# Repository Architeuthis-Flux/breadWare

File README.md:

# breadWare

# The vastly improved version of this is now [Jumperless](https://github.com/Architeuthis-Flux/Jumperless)
### This the early prototype version, and this lays out my thinking more on some fundamental desisions.

#### I've changed this project's name for version 3
The code and KiCAD files for the most recent revision are in the Jumperless folder. When I do a thorough writeup I may make an entirely new repo just so everythings stays clean. But for now, here's the new board and GUI 

# breadWare v0.2 
#### [Here's a link to the Hackaday.io project page](https://hackaday.io/project/180394-breadware)

My reason for doing this whole writeup and putting this out there is to hopefully find some fellow hackers who are equally stoked on breadWare and want to help make it into something where people will wonder how the hell they built anything before it existed (probably not Arduino levels of disruption, but when I need to use a Bus Pirate, I can't even imagine the horrible dystopian hellscape the world would be without it.) At least for me, placing jumpers messes up my flow, because there's always that angel on one shoulder telling me to be methodical: cut my jumpers to the right length, make nice 90° bends, use colors consistently, while the demon on the other shoulder says to just get the damn thing working now and let future me deal with the mess. The demon always wins, so I'd really like the angel to shut up, it's distracting. So offloading that internal debate to a computer seems like a good idea [disclaimer: do not run this on a HAL 9000 computer, I hear cognitive dissonance like this can cause undefined behavior]

So here's the second board revision. I was showing the [last version](breadWare/v0.1-alpha/) off to someone and they offhandedly mentioned that it would be cool if the whole thing fit under the breadboard. I knew this was my plan all along, but it forced me to finally design it before the code gets too specific to the original off-the-cuff design and I get stuck with my poor ~~life~~ design choices. 

## Matrix Board

I found that the most valuable resource when finding paths between rows that aren't directly connected (so they need to make an intermediate hop) are "virtual" breadboard rows that aren't connected to the actual board but connect to the control board below and basically act as the general purpose nodes to do everything else (like reading voltages, connecting to the GPIO on the microcontroller, connecting to a second board, etc.). I put 4 of them in (on chips A, D, E, H), and I don't think that's nearly enough if I want to be able to do a bunch of special function things at once without making the user use some particular set of rows to do certain things. I would really like to make it as simple as "put anything wherever and the board will figure it out."

I changed the logical arrangement of the [MT8816](https://www.futurlec.com/Datasheet/Zarlink/MT8816AE.pdf) crosspoint switches to make the it easier to just hop over the middle space. In the original layout if I wanted to connect top row 5 to bottom row 5, it would always take 2 hops to do that (and these switches each have an on resistance of about 65Ω). Now the bottom rows are flipped so internally the bottom left is 62 and counts down to 33 on the right (note: these are abstracted away to the user by using b1-b30 instead of bigger numbers.)

And just to add some glam I added some reverse mounted LEDs that shine through the top and bottom power rails to show when that rail's power supply is on.

## Control Board

I almost entirely redesigned the controller board so it has a ton of whatever the hardware equivalent of syntactic sugar is. The original was kind of thrown together to make sure the concept of using crosspoint switches like that wasn't fundamentally stupid (still not entirely ruling that out, but so far it looks promising.) I also just realized I never did a writeup for the first iteration, and I'm not about to go back and do that just to prove that this board is an improvement.

### Power Stuff
Because I'm going to such great lengths to make everything analog, and I already need a negative supply for the crosspoint switches; I decided to make the adjustable power supply for the rails also be able to do negative voltages. The power stuff still needs some work, right now it gets pretty warm when it's running and it really doesn't like it when I remove the matrix board with it on. Presumably because it needs some current draw but I'm not exactly sure why it cares as much as it does (I burned a tantalum cap shaped brand into my finger, you could almost read the markings in it.) 

Also, the range of voltages available to each of the 4 rails is fixed. Next revision might include some way to multiplex the power rails (allowing any of them to be negative, right now only the bottom negative rail can do that and it can be changed with a solder jumper) but having looked into it for a while, there doesn't seem to be a way to do it simply enough to outweigh the small utility gained from it. If anyone knows a better way to do this, let me know.

I'm using an [LT1054](https://www.ti.com/lit/ds/symlink/lt1054.pdf) switched capacitor bipolar voltage converter that takes in +5V and doubles it to +10V and also flips that to -10V. That powers the MT8816s directly and the op amps I'm using for the adjustable voltage supplies. The previous board used inductors for that, and aside from the electrical noise, you could hear them running. I know the frequency they run at is way higher than 20kHz but they must have been resonating with something (or I'm actually part bat) because it was super annoying.

The way I decided to make an adjustable supply that can be controlled by the mcu might be really dumb, but so far it seems to work. I didn't find any well documented examples of people doing it this way, so I'd love to hear from anyone who has or has a good reason why it will cause problems. 

I used an [MCP4728](http://ww1.microchip.com/downloads/en/devicedoc/22187e.pdf) DAC that's controlled by I2C and feeds it's 4 outputs into 2 [L272D](https://www.st.com/resource/en/datasheet/l272.pdf) power op amps that can apparently supply 1A each. I used the inverting arrangement with a gain of 1.6 to make the negative supply able to supply 0V - -8V from the 0V - +5V output from the DAC. I put a bunch of low voltage drop schottkys (or is it schottkies? weird) so whatever is happening on the power rails they're supplying shouldn't affect them too much. 

What's cool about this setup is that the DAC is fast enough to use this whole circuit as a DDS function generator. That's why I put solder jumpers to disconnect all the bypass caps. I haven't written the code to try this out yet though. 

### Special Functions

On the control board there's another 8x16 crosspoint switch that I'm using to multiplex the 8 passthrough connections (1 per chip on the top matrix board, but only 4 of them aren't connected to a breadboard pin) to the special functions on the bottom control board. 

The special functions are (a checkmark means the firmware is written enough to use it):
 [ ] 2 ADC channels that can be read by the microcontroller 
 [x] 2 digital potentiometer channels using an [MCP4661](https://ww1.microchip.com/downloads/en/DeviceDoc/22107B.pdf) 
 [ ] 5 GPIO pins directly connected to the [ATmega4809](http://ww1.microchip.com/downloads/en/DeviceDoc/ATmega4808-4809-Data-Sheet-DS40002173A.pdf)
 [x] 2 adjustable power supply channels (0 - 5V, 0 - -8V)
 [x] 1 ground

The 2 ADC channels go through two 4:1 voltage dividers to bring a possible ±10V input down to ±2.5V and the bottom of those dividers are connected to the V_REF pin on the microcontroller so analog signals can be biased to 0-5V to be read by the 10-bit ADC. 

There's an [MCP4661](https://ww1.microchip.com/downloads/en/DeviceDoc/22107B.pdf) dual 8 bit digital potentiometer that has all 3 pins on 2 independent pots connected to the special function switch. I need to come up with a better interface for setting it in the terminal menu. When I eventually get around to making a GUI for this it will definitely make these more useful. These also come in 4 different ranges (5K, 10K, 50K, 100K) with the same pinout, I currently have the 50K model in there so that means each step is 195 ohms.

The GPIO pins are super interesting, for some reason the [ATmega4809](http://ww1.microchip.com/downloads/en/DeviceDoc/ATmega4808-4809-Data-Sheet-DS40002173A.pdf) datasheet never mentions the clear superiority of the first 4 pins in port C. 

PC0-3 can do I2C, U(S)ART, 16-bit Timer/Counter, PWM, SPI, and CCL-LUT! 
The CCL-LUT means Configurable Custom Logic - LookUp Table, so that means it an simulate an arbitrary logic gate. The analog stuff is covered by pin PE3. 

Now the tricky part is coming up with a nice way to use those functions through the serial connection. I could probably somehow port the Bus Pirate firmware into some sort of shell, so you could use their awesome Community Firmware (and the red PCB really sells the aesthetic.) 

Also, if anyone from Dangerous Prototypes is reading this; I'm dying for updates on (or just an official crushing of my dreams of one day owning) the [Bus Pirate Ultra](http://dangerousprototypes.com/forum/index.php?topic=10316.0)

### Communicating With Other Things

On each corner of the board I put a 2x2 header so you can connect these side-by-side and make these into longer board. They communicate via UART with Tx Rx in at the top left and Tx Rx out at the top right. The bottom corners have the 4 unconnected pins from the top matrix on both sides. So you could use these to make connections from one board to the other. As it is currently, having only 4 of these general purpose matrix connections is a huge bottleneck for doing just about anything so I probably need to come up with a way to have more of these free pins in the next revision. 

To communicate with the computer, I'm using an [MCP2221A](http://ww1.microchip.com/downloads/en/devicedoc/20005565b.pdf) to talk to the mcu via a dedicated UART. That chip is also connected to the I2C lines but I'm not sure what I'm going to use that for, maybe I'll have the I2C traffic passed along in some sort of debug mode. It also can send a reset signal from one of it's 4 GPIO lines to the ATmega4809 (with a solder jumper in case that causes problems), which notably is a missing feature of this chip. 
I could pretend that my choice to to use this was some principled stand against FTDI to cover for the fact that I actually don't remember why I chose this over and FTDI232.

## Making It Do Stuff

The interface currently sort of follows the general format that a Bus Pirate (and I'm sure a bunch of other things) use; mostly single character commands that present a sub menu. It's amazing how quickly you run out of letters that make sense for a particular command, especially when you have some command you want to be available globally. 

Making connections on the board just requires you to type in the two rows you want to connect, separated by a comma. Rows on the bottom are preceded by a 'b' so if you want to connect the 12th row on the top to the 24th row on the bottom you just type
 > 12,b24

In the near future I intend to make a full blown GUI for this, because that's the part that will make this thing actually make your life easier.

Here are some screenshots the interface:

Connecting Nodes

Disconnecting Nodes

Turning on the power supplies

Using the potentiometer

Showing the frontend connections you've made

Showing the backend (chip to chip) connections 

Here are some extra glamour shots:

mmmmmm melty traces

 > btw most of these photos were taken on Lomochrome Metropolis with a Mamiya RB67
 > the two showing the boards separately were taken with an Intrepid 4x5 on cross-processed Provia 100f
 > you can download ridiculously huge scans of these (or my non-documentation related photos) from my [Flickr](https://www.flickr.com/photos/arabidsquid/)

## [Here's the documentation for v0.1](breadWare/v0.1-alpha/)

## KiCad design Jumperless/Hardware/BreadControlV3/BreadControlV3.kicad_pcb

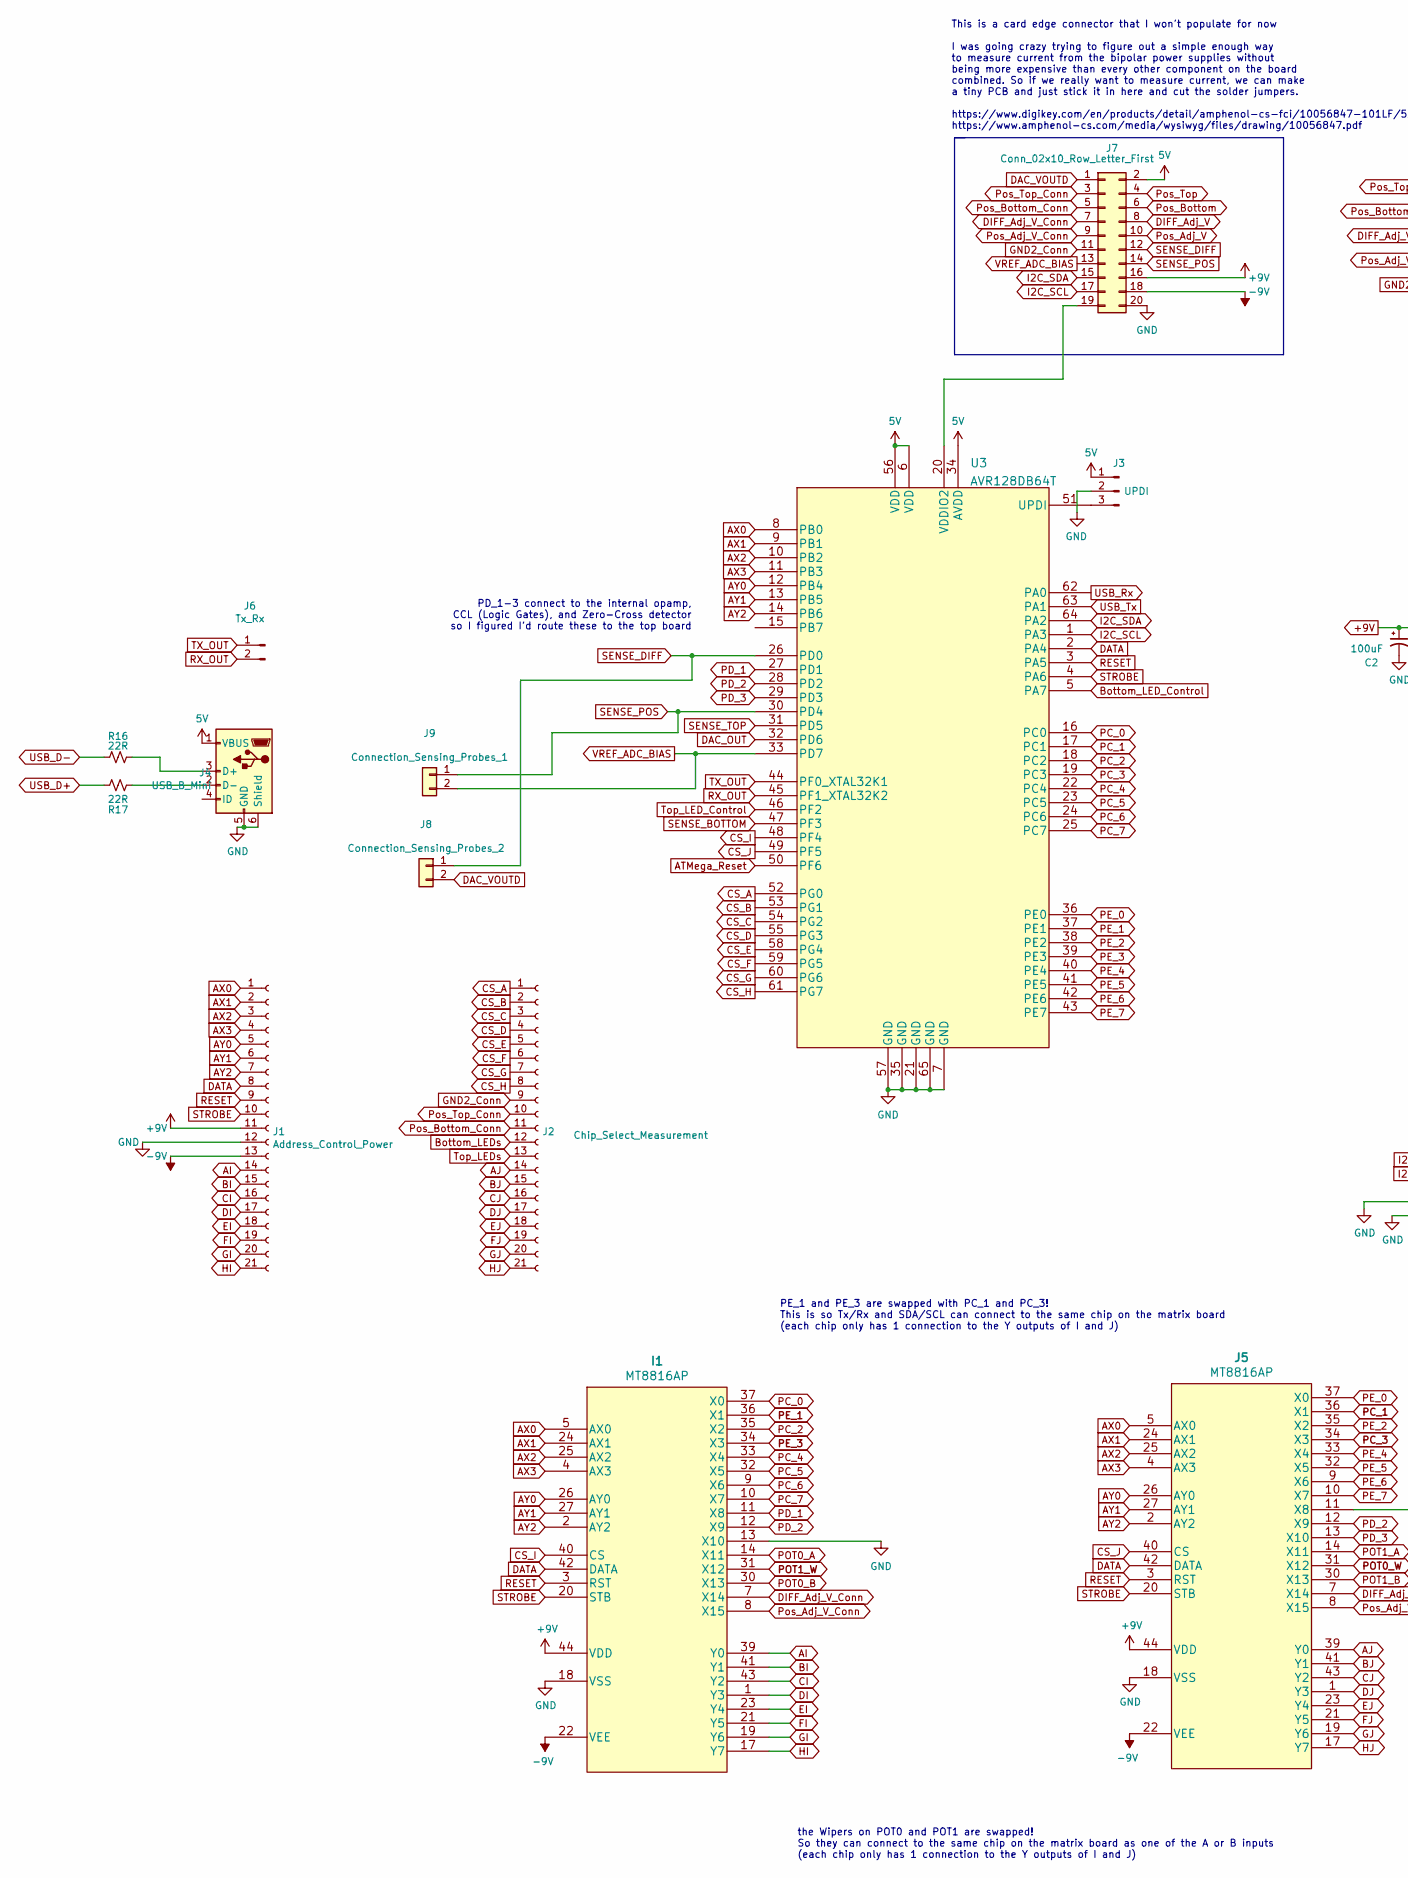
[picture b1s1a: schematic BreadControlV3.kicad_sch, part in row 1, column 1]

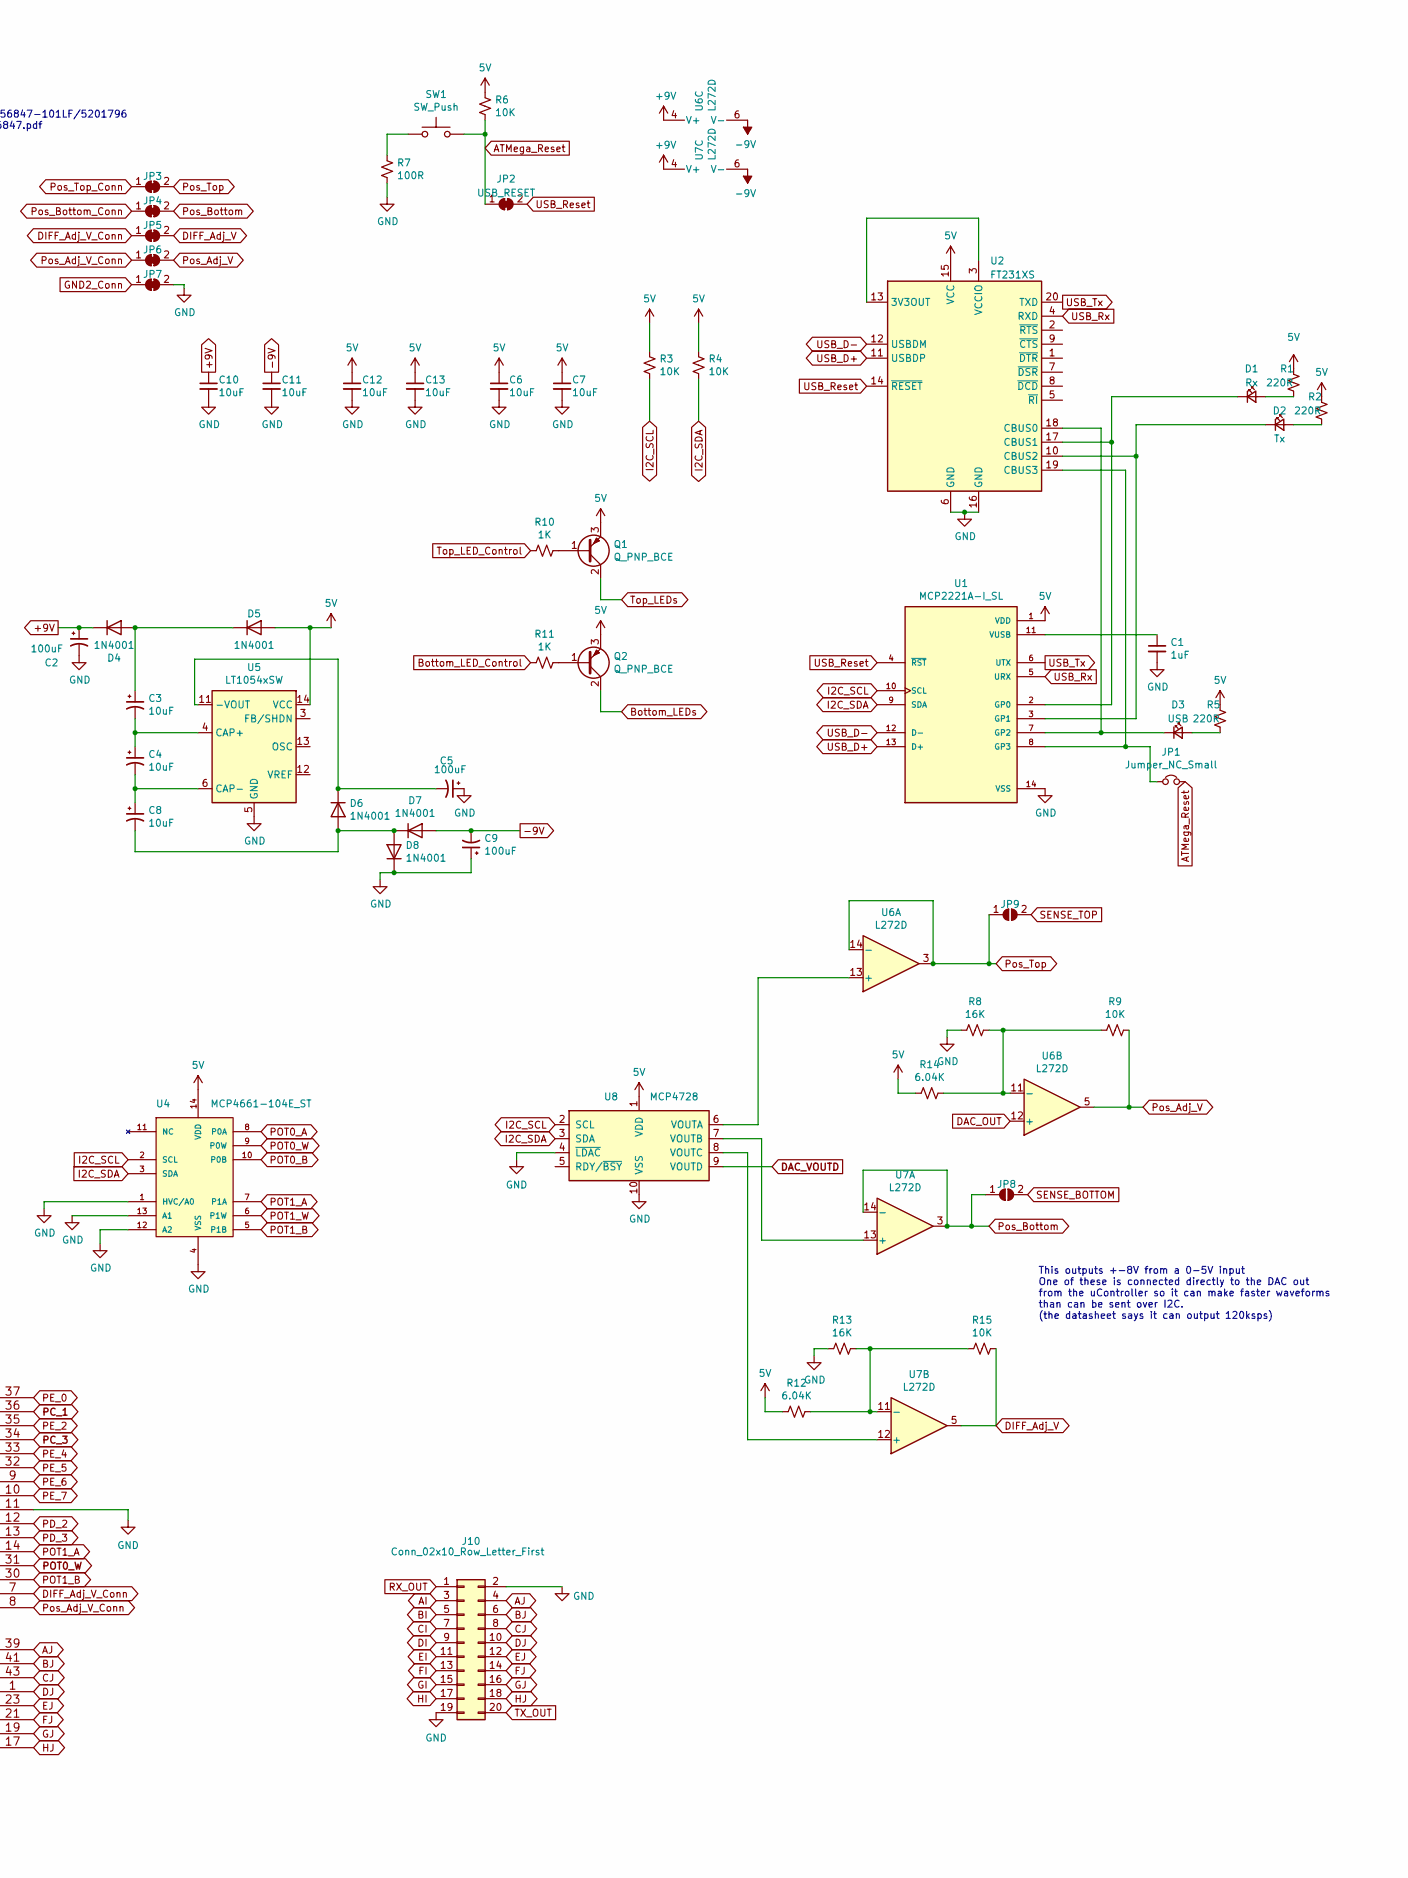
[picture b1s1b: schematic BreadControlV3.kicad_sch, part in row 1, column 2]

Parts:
C1: 1uF; C_0805_2012Metric_Pad1.18x1.45mm_HandSolder
C2, C5, C9: 100uF; C_1206_3216Metric_Pad1.33x1.80mm_HandSolder
C3, C4, C8: 10uF; CP_EIA-6032-20_AVX-F_Pad2.25x2.35mm_HandSolder
C6, C7, C10, C11, C12, C13: 10uF; C_0805_2012Metric_Pad1.18x1.45mm_HandSolder
D1: Rx; D_0805_2012Metric_Pad1.15x1.40mm_HandSolder
D2: Tx; D_0805_2012Metric_Pad1.15x1.40mm_HandSolder
D3: USB; D_0805_2012Metric_Pad1.15x1.40mm_HandSolder
D4, D5, D6, D7, D8: 1N4001; D_SOD-123
I1: MT8816AP; PLCC-44_16.6x16.6mm_P1.27mm
J1: Address_Control_Power; PinHeader_1x21_P2.54mm_Vertical
J2: Chip_Select_Measurement; PinHeader_1x21_P2.54mm_Vertical
J3: UPDI; PinHeader_1x03_P2.54mm_Vertical
J4: USB_B_Mini; USB_Mini-B_Wuerth_65100516121_Horizontal
J5: MT8816AP; PLCC-44_16.6x16.6mm_P1.27mm
J6: Tx_Rx; PinHeader_1x02_P2.54mm_Vertical
J7, J10: Conn_02x10_Row_Letter_First; 10056847-101LF
J8: Connection_Sensing_Probes_2; PinHeader_1x02_P2.54mm_Vertical
J9: Connection_Sensing_Probes_1; PinHeader_1x02_P2.54mm_Vertical
JP1: Jumper_NC_Small; SolderJumper-2_P1.3mm_Bridged_RoundedPad1.0x1.5mm
JP2: USB_RESET; SolderJumper-2_P1.3mm_Bridged_RoundedPad1.0x1.5mm
JP3, JP4, JP5, JP6, JP7: SolderJumper_2_Bridged; SolderJumper-2_P1.3mm_Bridged_RoundedPad1.0x1.5mm
JP8, JP9: SolderJumper_2_Open; SolderJumper-2_P1.3mm_Open_RoundedPad1.0x1.5mm
Q1, Q2: Q_PNP_BCE; SOT-23
R1, R2, R5: 220R; R_0805_2012Metric_Pad1.20x1.40mm_HandSolder
R3, R4, R6, R9, R15: 10K; R_0805_2012Metric_Pad1.20x1.40mm_HandSolder
R7: 100R; R_0805_2012Metric_Pad1.20x1.40mm_HandSolder
R8, R13: 16K; R_0805_2012Metric_Pad1.20x1.40mm_HandSolder
R10, R11: 1K; R_0805_2012Metric_Pad1.20x1.40mm_HandSolder
R12, R14: 6.04K; R_0805_2012Metric_Pad1.20x1.40mm_HandSolder
R16, R17: 22R; R_0805_Optional_Bridged
SW1: SW_Push; SW_SPST_PTS645
U1: MCP2221A-I_SL; SOIC-14_3.9x8.7mm_P1.27mm
U2: FT231XS; SSOP-20_3.9x8.7mm_P0.635mm
U3: AVR128DB64T; VQFN-64-1EP_9x9mm_P0.5mm_EP7.15x7.15mm
U4: MCP4661-104E_ST; TSSOP-14_4.4x5mm_P0.65mm; MPN MCP4661-104E/ST
U5: LT1054xSW; SOIC-16W_7.5x10.3mm_P1.27mm
U6, U7: L272D; SOIC-16_3.9x9.9mm_P1.27mm
U8: MCP4728; MSOP-10_3x3mm_P0.5mm

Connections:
5V: C6.1, C7.1, C12.1, C13.1, D5.2 (A), J3.1, J4.1 (VBUS), J7.2, Q1.3 (E), Q2.3 (E), R1.1, R2.1, R3.1, R4.1, R5.1, R6.1, R12.1, R14.1, U1.1 (VDD), U2.15 (VCC), U3.6 (VDD), U3.34 (AVDD), U3.56 (VDD), U4.14 (VDD), U5.14 (VCC), U8.1 (VDD)
+9V: C2.1, C10.1, D4.1 (K), I1.44 (VDD), J1.11, J5.44 (VDD), J7.16, U6.4 (V+), U7.4 (V+)
-9V: C9.2, C11.1, D7.2 (A), I1.22 (VEE), J1.13, J5.22 (VEE), J7.18, U6.6 (V-), U7.6 (V-)
AI: I1.39 (Y0), J1.14, J10.3
AJ: J2.14, J5.39 (Y0), J10.4
ATMega_Reset: JP1.2, JP2.1 (A), R6.2, SW1.2, U3.50 (PF6)
AX0: I1.5 (AX0), J1.1, J5.5 (AX0), U3.8 (PB0)
AX1: I1.24 (AX1), J1.2, J5.24 (AX1), U3.9 (PB1)
AX2: I1.25 (AX2), J1.3, J5.25 (AX2), U3.10 (PB2)
AX3: I1.4 (AX3), J1.4, J5.4 (AX3), U3.11 (PB3)
AY0: I1.26 (AY0), J1.5, J5.26 (AY0), U3.12 (PB4)
AY1: I1.27 (AY1), J1.6, J5.27 (AY1), U3.13 (PB5)
AY2: I1.2 (AY2), J1.7, J5.2 (AY2), U3.14 (PB6)
BI: I1.41 (Y1), J1.15, J10.5
BJ: J2.15, J5.41 (Y1), J10.6
Bottom_LED_Control: R11.2, U3.5 (PA7)
Bottom_LEDs: J2.12, Q2.2 (C)
CI: I1.43 (Y2), J1.16, J10.7
CJ: J2.16, J5.43 (Y2), J10.8
CS_A: J2.1, U3.52 (PG0)
CS_B: J2.2, U3.53 (PG1)
CS_C: J2.3, U3.54 (PG2)
CS_D: J2.4, U3.55 (PG3)
CS_E: J2.5, U3.58 (PG4)
CS_F: J2.6, U3.59 (PG5)
CS_G: J2.7, U3.60 (PG6)
CS_H: J2.8, U3.61 (PG7)
CS_I: I1.40 (CS), U3.48 (PF4)
CS_J: J5.40 (CS), U3.49 (PF5)
DAC_OUT: U3.32 (PD6), U6.12 (+)
DAC_VOUTD: J7.1, J8.2, U8.9 (VOUTD)
DATA: I1.42 (DATA), J1.8, J5.42 (DATA), U3.2 (PA4)
DI: I1.1 (Y3), J1.17, J10.9
DIFF_Adj_V: J7.8, JP5.2 (B), R15.2, U7.5
DIFF_Adj_V_Conn: I1.7 (X14), J5.7 (X14), J7.7, JP5.1 (A)
DJ: J2.17, J5.1 (Y3), J10.10
EI: I1.23 (Y4), J1.18, J10.11
EJ: J2.18, J5.23 (Y4), J10.12
FI: I1.21 (Y5), J1.19, J10.13
FJ: J2.19, J5.21 (Y5), J10.14
GI: I1.19 (Y6), J1.20, J10.15
GJ: J2.20, J5.19 (Y6), J10.16
GND: C1.2, C2.2, C5.1, C6.2, C7.2, C9.1, C10.2, C11.2, C12.2, C13.2, D8.1 (K), I1.13 (X10), I1.18 (VSS), J1.12, J3.2, J4.5 (GND), J4.6 (Shield), J5.11 (X8), J5.18 (VSS), J7.20, J10.2, J10.19, JP7.2 (B), R7.2, R8.1, R13.1, U1.14 (VSS), U2.6 (GND), U2.16 (GND), U3.7 (GND), U3.21 (GND), U3.35 (GND), U3.57 (GND), U3.65 (GND), U4.1 (HVC/A0), U4.4 (VSS), U4.12 (A2), U4.13 (A1), U5.5 (GND), U8.4 (~LDAC), U8.10 (VSS)
GND2_Conn: J2.9, J7.11, JP7.1 (A)
HI: I1.17 (Y7), J1.21, J10.17
HJ: J2.21, J5.17 (Y7), J10.18
I2C_SCL: J7.17, R3.2, U1.10 (SCL), U3.1 (PA3), U4.2 (SCL), U8.2 (SCL)
I2C_SDA: J7.15, R4.2, U1.9 (SDA), U3.64 (PA2), U4.3 (SDA), U8.3 (SDA)
unnamed: C1.1, U1.11 (VUSB)
unnamed: C3.1, D4.2 (A), D5.1 (K)
unnamed: C3.2, C4.1, U5.4 (CAP+)
unnamed: C4.2, C8.1, U5.6 (CAP-)
unnamed: C5.2, D6.1 (K), U5.11 (-VOUT)
unnamed: C8.2, D6.2 (A), D7.1 (K), D8.2 (A)
unnamed: D1.1 (K), U1.2 (GP0), U2.17 (CBUS1)
unnamed: D1.2 (A), R1.2
unnamed: D2.1 (K), U1.3 (GP1), U2.10 (CBUS2)
unnamed: D2.2 (A), R2.2
unnamed: D3.1 (K), U1.7 (GP2), U2.18 (CBUS0)
unnamed: D3.2 (A), R5.2
unnamed: J3.3, U3.51 (UPDI)
unnamed: J4.2 (D-), R17.1
unnamed: J4.3 (D+), R16.1
unnamed: J7.19, U3.20 (VDDIO2)
unnamed: JP1.1, U1.8 (GP3), U2.19 (CBUS3)
unnamed: Q1.1 (B), R10.1
unnamed: Q2.1 (B), R11.1
unnamed: R7.1, SW1.1
unnamed: R12.2, R13.2, R15.1, U7.11 (-)
unnamed: R8.2, R9.1, R14.2, U6.11 (-)
unnamed: U2.3 (VCCIO), U2.13 (3V3OUT)
unnamed: U6.13 (+), U8.6 (VOUTA)
unnamed: U7.12 (+), U8.8 (VOUTC)
unnamed: U7.13 (+), U8.7 (VOUTB)
PC_0: I1.37 (X0), U3.16 (PC0)
PC_1: J5.36 (X1), U3.17 (PC1)
PC_2: I1.35 (X2), U3.18 (PC2)
PC_3: J5.34 (X3), U3.19 (PC3)
PC_4: I1.33 (X4), U3.22 (PC4)
PC_5: I1.32 (X5), U3.23 (PC5)
PC_6: I1.9 (X6), U3.24 (PC6)
PC_7: I1.10 (X7), U3.25 (PC7)
PD_1: I1.11 (X8), U3.27 (PD1)
PD_2: I1.12 (X9), J5.12 (X9), U3.28 (PD2)
PD_3: J5.13 (X10), U3.29 (PD3)
PE_0: J5.37 (X0), U3.36 (PE0)
PE_1: I1.36 (X1), U3.37 (PE1)
PE_2: J5.35 (X2), U3.38 (PE2)
PE_3: I1.34 (X3), U3.39 (PE3)
PE_4: J5.33 (X4), U3.40 (PE4)
PE_5: J5.32 (X5), U3.41 (PE5)
PE_6: J5.9 (X6), U3.42 (PE6)
PE_7: J5.10 (X7), U3.43 (PE7)
POT0_A: I1.14 (X11), U4.8 (P0A)
POT0_B: I1.30 (X13), U4.10 (P0B)
POT0_W: J5.31 (X12), U4.9 (P0W)
POT1_A: J5.14 (X11), U4.7 (P1A)
POT1_B: J5.30 (X13), U4.5 (P1B)
POT1_W: I1.31 (X12), U4.6 (P1W)
Pos_Adj_V: J7.10, JP6.2 (B), R9.2, U6.5
Pos_Adj_V_Conn: I1.8 (X15), J5.8 (X15), J7.9, JP6.1 (A)
Pos_Bottom: J7.6, JP4.2 (B), JP8.1 (A), U7.3, U7.14 (-)
Pos_Bottom_Conn: J2.11, J7.5, JP4.1 (A)
Pos_Top: J7.4, JP3.2 (B), JP9.1 (A), U6.3, U6.14 (-)
Pos_Top_Conn: J2.10, J7.3, JP3.1 (A)
RESET: I1.3 (RST), J1.9, J5.3 (RST), U3.3 (PA5)
RX_OUT: J6.2, J10.1, U3.45 (PF1_XTAL32K2)
SENSE_BOTTOM: JP8.2 (B), U3.47 (PF3)
SENSE_DIFF: J7.12, J8.1, U3.26 (PD0)
SENSE_POS: J7.14, J9.1, U3.30 (PD4)
SENSE_TOP: JP9.2 (B), U3.31 (PD5)
STROBE: I1.20 (STB), J1.10, J5.20 (STB), U3.4 (PA6)
TX_OUT: J6.1, J10.20, U3.44 (PF0_XTAL32K1)
Top_LED_Control: R10.2, U3.46 (PF2)
Top_LEDs: J2.13, Q1.2 (C)
USB_D+: R17.2, U1.13 (D+), U2.11 (USBDP)
USB_D-: R16.2, U1.12 (D-), U2.12 (USBDM)
USB_Reset: JP2.2 (B), U1.4 (~RST), U2.14 (~RESET)
USB_Rx: U1.5 (URX), U2.4 (RXD), U3.62 (PA0)
USB_Tx: U1.6 (UTX), U2.20 (TXD), U3.63 (PA1)
VREF_ADC_BIAS: J7.13, J9.2, U3.33 (PD7)

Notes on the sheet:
This is a card edge connector that I won't populate for now I was going crazy trying to figure out a simple enough way to measure current from the bipolar power supplies without being more expensive than every other component on the board combined. So if we really want to measure current, we can ma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
PD_1-3 connect to the internal opamp, CCL (Logic Gates), and Zero-Cross detector so I figured I'd route these to the top board
This outputs +-8V from a 0-5V input One of these is connected directly to the DAC out from the uController so it can make faster waveforms than can be sent over I2C. (the datasheet says it can output 120ksps)
PE_1 and PE_3 are swapped with PC_1 and PC_3! This is so Tx/Rx and SDA/SCL can connect to the same chip on the matrix board (each chip only has 1 connection to the Y outputs of I and J)
the Wipers on POT0 and POT1 are swapped! So they can connect to the same chip on the matrix board as one of the A or B inputs (each chip only has 1 connection to the Y outputs of I and J)

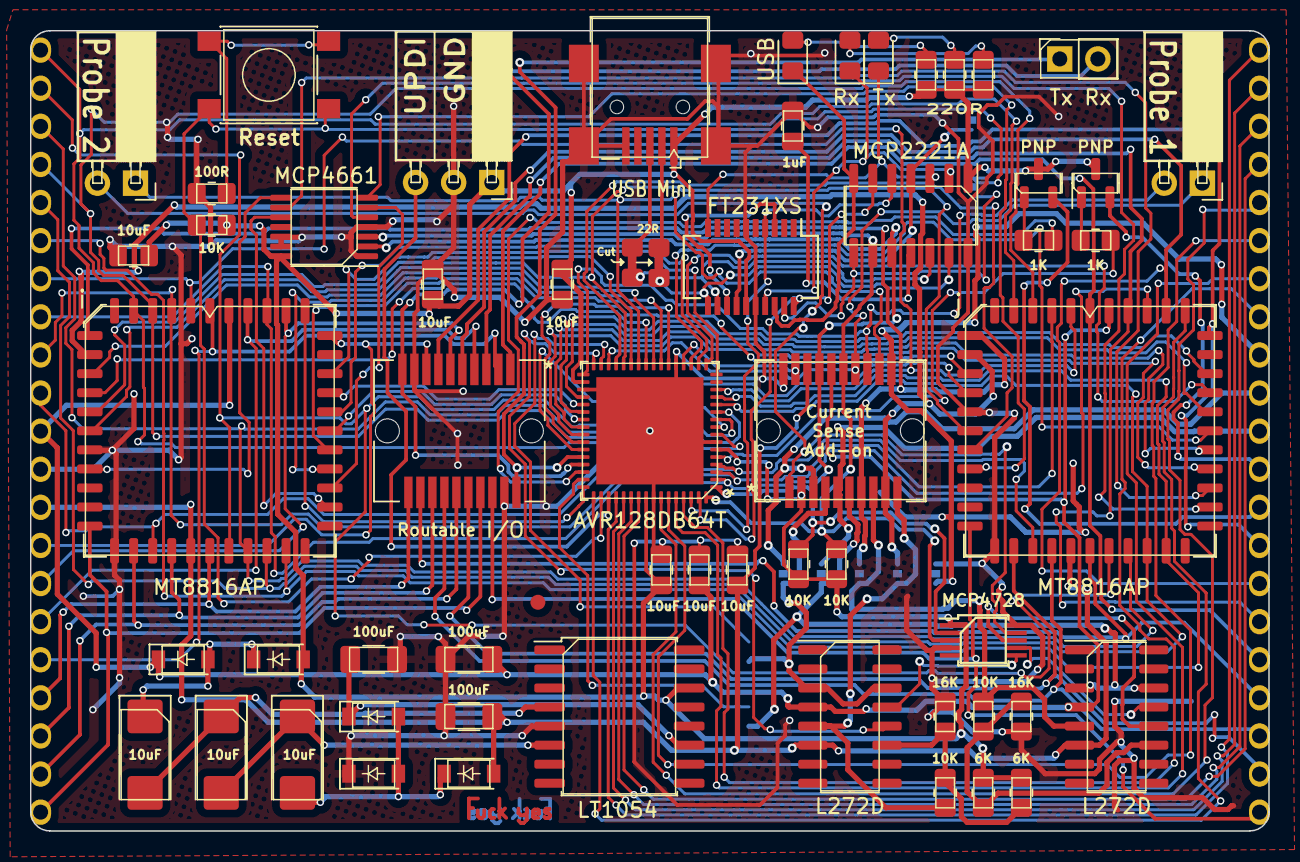
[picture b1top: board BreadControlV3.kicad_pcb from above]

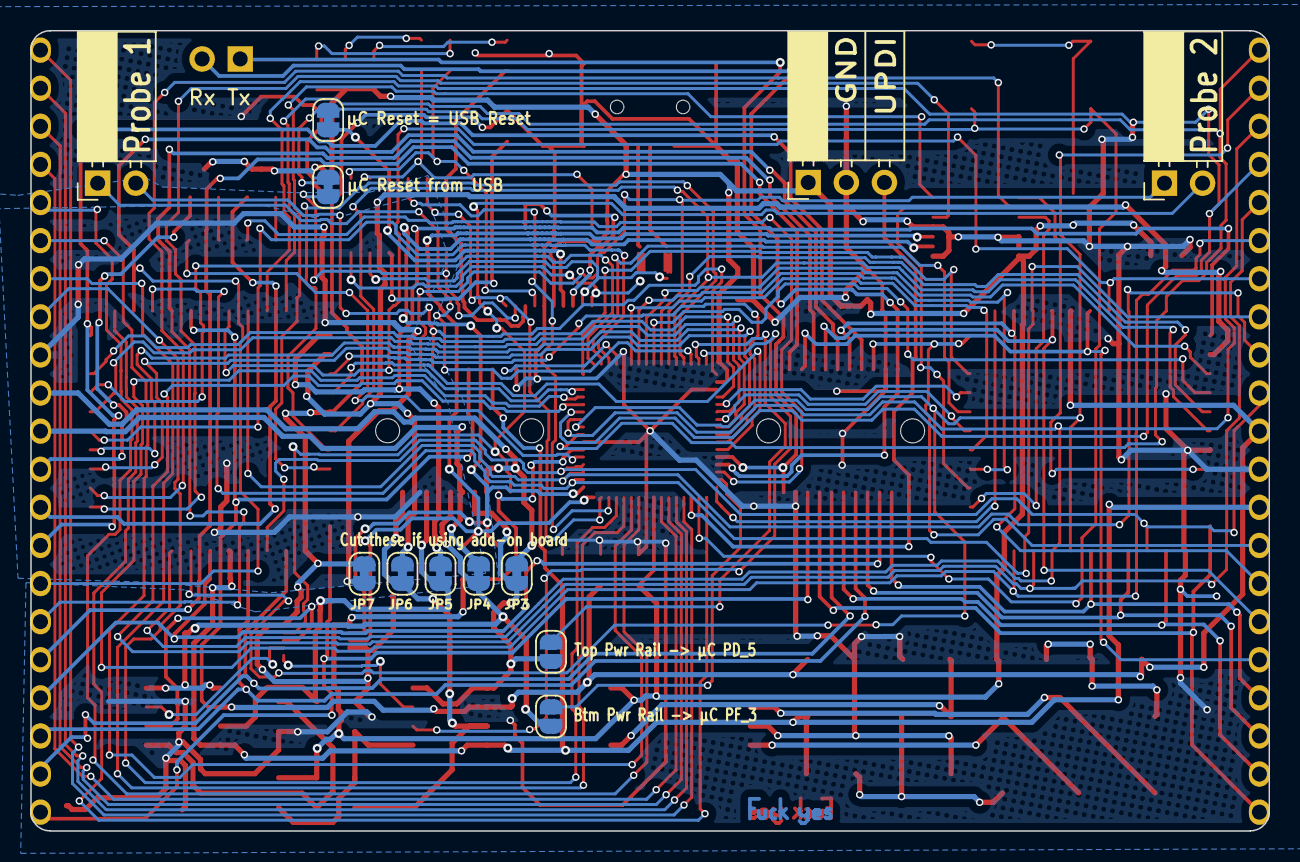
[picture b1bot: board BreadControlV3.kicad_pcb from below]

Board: 2 copper layers, 82.5 x 53.3 mm, 69 parts (9 on the bottom side), 121 nets.
